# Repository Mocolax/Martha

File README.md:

# Martha: simulación, hardware y navegación PPO

Martha usa el mismo contrato ROS 2 en Gazebo y en el robot físico. El backend
se selecciona en el launch; teleoperación, RViz, SLAM y la política PPO no
cambian de tópicos.

| Interfaz | Simulación | Hardware |
|---|---|---|
| Comando | `/cmd_vel` (`Twist`) | `/cmd_vel` (`Twist`) |
| LiDAR | `/scan` | `/scan` |
| IMU | `/imu/data` | `/imu/data` |
| Odometría para consumidores | `/odometry/filtered` | `/odometry/filtered` |
| Meta | `/goal_pose` | `/goal_pose` |
| TF dinámico | `odom -> base_link` por EKF | `odom -> base_link` por EKF |
| Reloj | simulado | sistema |

SLAM Toolbox es la única autoridad de `map -> odom` cuando `mapping:=true`.
El controlador y el firmware entregan las mediciones de ruedas; el EKF es la
única autoridad dinámica de `odom -> base_link`.

## Construcción

Requiere Ubuntu 22.04 y ROS 2 Humble con Gazebo Classic. Desde el workspace:

```bash
cd ~/ros2_ws
rosdep install --from-paths src --ignore-src -r -y
python3 -m pip install -r src/martha/requirements-ppo.txt
colcon build --packages-select martha --symlink-install
source install/setup.bash
```

## Simulación

Arranque común sin SLAM:

```bash
ros2 launch martha bringup.launch.py mode:=sim mapping:=false
```

Este es el launcher canónico. `simulation.launch.py` y `hardware.launch.py`
son los backends que compone internamente.

Teleoperación, en otra terminal con el workspace cargado:

```bash
ros2 run teleop_twist_keyboard teleop_twist_keyboard \
  --ros-args -r cmd_vel:=/cmd_vel
```

Mapeo y RViz:

```bash
ros2 launch martha bringup.launch.py mode:=sim mapping:=true
```

Para guardar el mapa construido:

```bash
ros2 service call /slam_toolbox/save_map slam_toolbox/srv/SaveMap \
  "{name: {data: '/ruta/absoluta/mapa_martha'}}"
```

## Hardware

Antes del launch deben cumplirse estas condiciones:

1. La ESP32 ejecuta el firmware de `arduino/` y aparece en un puerto estable,
   preferiblemente `/dev/serial/by-id/...`.
2. El RPLIDAR A2M8 está conectado y tiene disponible el enlace estable
   `/dev/rplidar`.
3. La polaridad de motores y encoders, el radio de rueda y la geometría
   mecanum se comprobaron físicamente con las ruedas levantadas.

En cada computadora anfitriona, instala una vez la regla udev incluida en
`rplidar_ros` y vuelve a conectar el LiDAR:

```bash
sudo cp ~/ros2_ws/src/rplidar_ros/scripts/rplidar.rules \
  /etc/udev/rules.d/99-rplidar.rules
sudo udevadm control --reload-rules
sudo udevadm trigger
ls -l /dev/rplidar
```

El launch de hardware inicia `rplidar_node` con el perfil A2M8: 115200
baudios, modo `Sensitivity`, compensación angular, 10 Hz, tópico `/scan` y
frame `lidar`. Arranque completo:

```bash
ros2 launch martha bringup.launch.py \
  mode:=hardware \
  port:=/dev/serial/by-id/PUERTO_DE_LA_ESP32 \
  lidar_port:=/dev/rplidar \
  mapping:=true
```

El puerto puede sobrescribirse con `lidar_port:=...`. Si la ESP32 también usa
un adaptador CP210x, utiliza rutas distintas de `/dev/serial/by-id`; el launch
rechaza ambos argumentos si terminan apuntando al mismo dispositivo. Para usar
un driver iniciado externamente, añade `start_lidar:=false`.

El URDF sitúa el plano del LiDAR al frente y centrado, aproximadamente a
`x=0.2325 m` de `base_link`. El montaje físico debe respetar esa posición; si
cambia, deben actualizarse juntos el URDF y el offset usado por la protección
de huella PPO.

El mismo comando de `teleop_twist_keyboard` usado en simulación mueve el
hardware. Comprobaciones mínimas:

```bash
ros2 topic hz /scan
ros2 topic echo --once /scan
ros2 topic hz /odometry/filtered
ros2 topic echo --once /hardware/motor_fault
ros2 run tf2_ros tf2_echo odom base_link
ros2 run tf2_ros tf2_echo base_link lidar
```

El puente limita los comandos a `vx=0.35 m/s`, `vy=0.35 m/s` y
`wz=0.80 rad/s`; rechaza valores no finitos, vigila la telemetría serial y
publica el fault latched `/hardware/motor_fault`. Para rearmar una protección:

```bash
ros2 service call \
  /cmd_vel_serial_bridge/reset_motor_protection \
  std_srvs/srv/Trigger "{}"
ros2 topic pub --once /cmd_vel geometry_msgs/msg/Twist "{}"
```

El segundo comando cero debe enviarse después del reconocimiento de la ESP32.

## Entrenamiento PPO en Gazebo

Los escenarios canónicos son `four_rooms`, `hall`, `multi`, `roblab`, `room`
y `tube`. El entrenamiento genera un único mundo temporal con las seis arenas
en una cuadrícula 3×2, separadas 30 m, y lanza ocho robots namespaced
(`martha_0` a `martha_7`) dentro de un solo `gzserver`.

Los inicios y metas se editan únicamente en `config/training_points.yaml`.
Cada coordenada es local al `.world`; el coordinador aplica el desplazamiento
de su arena. `x` e `y` son obligatorios y `yaw: null` pide una orientación de
inicio aleatoria. Un mismo punto puede ser inicio o meta, pero no ambos para la
misma Martha. Antes de lanzar Gazebo se validan IDs, valores finitos, espacio
libre, conectividad, distancia mínima y ocho inicios simultáneos separados. No
hay generación automática: mientras una sección tenga menos de ocho puntos
válidos, `ppo_train` termina indicando el mapa problemático.

La observación contiene cuatro frames distribuidos durante un segundo de tiempo
ROS. Cada frame reúne 36 sectores LiDAR, distancia normalizada y seno/coseno del
rumbo hacia un waypoint local, además de velocidad odométrica `[Vx, Vy, W]`; el
vector completo tiene 168 valores. La distancia se codifica sin recorte como
`d / (d + 3 m)`. En Gazebo, el planificador privilegiado usa el mapa y la pose
real para actualizar un waypoint geodésico a 0.50 m; la política solo recibe
sus tres características relativas, no el mapa ni las coordenadas globales.
La llegada y las métricas siguen midiéndose contra la meta final. En el robot
real, un planificador global con localización debe producir el mismo waypoint.
La recompensa combina avance, penalización por paso, esfuerzo, cambios bruscos,
proximidad, colisión y llegada.

Cada robot publica contactos de su huella elevada en
`/martha_N/contacts` mediante `libgazebo_ros_bumper.so`. Los contactos con
suelo o con el propio modelo se ignoran; una pared u otra Martha finaliza el
episodio. Si chocan dos robots, ambos terminan. El LiDAR no decide colisiones:
se conserva para observación, recompensa de proximidad y validación del reset.

La cantidad original de puntos de `/scan` no cambia el tamaño del modelo: los
scans de densidad variable del A2M8 se agrupan angularmente por mínimo en los
mismos 36 sectores y se limitan al alcance común de 8 m.

El actor y el crítico tienen extractores multirrama independientes. La variable
`OBSERVATION_ENCODER_MODE` de `martha/PPO/network.py` selecciona `"present"`
(solo el frame más reciente) o `"history"` (los cuatro frames) como entrada de
las ramas de LiDAR, distancia, orientación y velocidad. El modo normal es
`"present"`; el entorno conserva el vector canónico de 168 valores, pero el
extractor ignora los tres frames antiguos y deja la temporalidad al LSTM. Las
ramas se fusionan en 384 unidades y luego el actor y el crítico usan su propia
LSTM de 128 unidades. Cambiar el modo exige entrenar un checkpoint nuevo.
Cada robot conserva memoria recurrente independiente; se borra al iniciar un
episodio, cambiar de meta, llegar o entrar en fault. PPO entrena fragmentos
ordenados de 32 pasos con máscaras de padding y de fin de episodio, sin barajar
transiciones temporales aisladas. Sus gradientes se recortan por separado. La
recompensa guardada en el
buffer se multiplica por `reward_scale` (`0.01` por defecto), pero
`episode_reward` conserva la recompensa original y `episode_scaled_reward`
registra el valor usado por PPO.

Los valores de entrenamiento estan reunidos al principio de
`martha/PPO/train.py`, en `TrainingDefaults`. Para cambiar permanentemente el
numero de robots, velocidad, episodios o hiperparametros, edita ese unico
bloque. El unico argumento de consola es `--resume`.

Las ocho Marthas comparten un escenario durante una ronda. Sus inicios no se
repiten; cada meta difiere del inicio propio. Al terminar por meta, contacto o
timeout, el robot se detiene, pierde su marcador y se teletransporta a una
plaza exclusiva alrededor de `y=-43 m`. Allí espera sin bloquear la arena.
Cuando termina la última Martha activa comienza la ronda siguiente. Cada ciclo
baraja los seis escenarios con la semilla del entrenamiento y usa cada uno una
sola vez. `map_index` fija todas las rondas a un único escenario. `episodes`
sigue contando episodios individuales, por lo que la última ronda puede activar
menos de ocho robots.

La recompensa se configura en `martha/PPO/reward.py`, dentro de
`RewardConfig`. Sigue la función completa de Jestel et al.,
[*Obtaining Robust Control and Navigation Policies for Multi-Robot Navigation
via Deep Reinforcement Learning*](https://arxiv.org/pdf/2209.03097). Para un
step no terminal se calcula:

```text
delta_d = distancia_euclidea_anterior - distancia_euclidea_actual
distancia = delta_d * (0.002 si delta_d < 0, de otro modo 0.01)
orientacion = (1 - 2 * abs(angulo_meta) / pi) *
              0.001, solo si Martha apunta a ±90° de la meta; si no, 0
record = 0.05 * (mejor_distancia_del_episodio - distancia_actual)
         solo cuando establece un nuevo récord
laser = -0.01 * (0.65 - minimo_laser), solo bajo 0.65 m
zigzag = -0.01, si hay más de 3 reversos directos izquierda-derecha
          durante las últimas 10 acciones
reward = costo_temporal + distancia + orientacion + record + laser + zigzag
```

La distancia para recompensa es euclídea; la distancia geodésica de Gazebo se
mantiene únicamente para SPL y las métricas de ruta. Cada transición no terminal
aplica un costo temporal de `-0.0002`. Los finales son exclusivos: meta `+1.0`,
colisión/motor fault/fuera del mapa `-0.75` y timeout `-0.5`.
Una colisión conserva prioridad sobre una señal simultánea de meta. El zigzag
usa la velocidad angular aplicada: izquierda por encima de `+0.2 rad/s`,
derecha por debajo de `-0.2 rad/s`; una acción recta corta la secuencia. Esos
tres parámetros no fueron publicados por el paper y son la adaptación acordada
para Martha. Los checkpoints nuevos guardan `reward_config`; al reanudar o
evaluar uno antiguo se usan los valores actuales y aparece una advertencia.

El entrenamiento siempre administra su propia instancia de Gazebo. No
inicies `simulation.launch.py` antes de `ppo_train`, ni siquiera cuando
`num_envs=1`. El perfil PPO usa por defecto un paso físico de 2 ms, 180 rayos
LiDAR reducidos a los mismos 36 sectores y cinemática planar. La simulación
normal conserva por defecto el modelo detallado de 48 rodillos por robot, el
paso de 1 ms y 360 rayos. Por tanto, el contrato de observación y los tópicos
ROS son comunes, pero el backend de entrenamiento evita simular articulaciones
que no aportan información a la política.

Si el factor supera la capacidad del equipo, Gazebo simplemente no alcanzara
la velocidad solicitada y pueden aparecer jitter, colas de mensajes o
`sensor_timeout` en las metricas. En ese caso reduce el factor; aumentar el
valor mas alla del rendimiento sostenible no acelera el aprendizaje.

Para entrenar:

```bash
cd ~/ros2_ws
source install/setup.bash
ros2 run martha ppo_train
```

`TrainingDefaults.num_envs=4` significa cantidad de robots, no cantidad de
servidores. En cada paso vectorizado el coordinador publica todas las acciones,
reanuda la física una vez, recibe sensores/contactos frescos y la pausa una
vez. Cuando uno termina, su plaza se recicla en el mismo mapa; el intervalo de
asentamiento se registra como transición de parada para los robots activos y
queda enmascarado del loss del actor, aunque sí entrena al crítico. El único log
de simulación queda en `<run>/gazebo.log`. Con `gazebo_gui=True`, una ventana
muestra las seis arenas y la flota.
El arranque es secuencial para evitar carreras de Gazebo y puede tardar varios
minutos con los modelos detallados; `gazebo_startup_timeout` vale 240 s.

Las evaluaciones periódicas esperan el final de un bloque. Los demás robots quedan
aparcados y `martha_0` evalúa la política dentro del mismo `gzserver`. Cambia
`eval_every`, `eval_map_count`, `num_envs`, `map_batch_episodes` y
`sim_speed_factor` en
`TrainingDefaults`; `eval_every=0` desactiva la evaluación periódica. En
entrenamiento no abras otro `simulation.launch.py`: el coordinador es dueño de
la única simulación.

Cada intento deja de asignar episodios 30 minutos antes del límite de 24 horas,
drena los episodios activos y guarda un checkpoint. Si alcanza el límite duro,
los episodios restantes se cierran como truncamientos con bootstrap. El CSV
incluye tiempo acumulado de física, reset, PPO, evaluación y checkpoint, además
de `training_steps_per_second`.

Cuando no haya un entrenamiento activo, compara 1, 2 y 4 robots con una carga
fija y sin actualizar la política:

```bash
ros2 run martha ppo_benchmark
```

El benchmark se niega a competir por recursos si detecta `ppo_train` activo.
Para validar ademas el reciclaje de un robot mientras sus pares siguen activos:

```bash
ros2 run martha ppo_benchmark --robot-counts 4 --steps 40 --recycle-smoke
```

Los resultados quedan por defecto en
`~/ros2_ws/src/martha/martha/PPO/ppo_runs/<run>/`: `metrics.csv`,
`last_model.pt`, `best_model.pt`, `learning_report.png`,
`ppo_diagnostics.png` y `training_summary.txt`. Los tres informes se generan
automáticamente al finalizar correctamente. El mejor modelo se elige por tasa de éxito,
SPL, menor tasa de colisión y, al final, recompensa. La ubicación se configura
con `TrainingDefaults.runs_dir`. `metrics.csv` incluye `approx_kl`,
`clip_fraction`, `explained_variance`, `policy_std`, `actor_inactive_relu` y
`critic_inactive_relu` para detectar inestabilidad antes de que la politica
deje de responder a sus observaciones. Para continuar un checkpoint se debe
conservar el mismo `reward_scale`:

```bash
ros2 run martha ppo_train \
  --resume /ruta/ppo_runs/run/last_model.pt
```

Antes de reanudar, establece en `TrainingDefaults.episodes` el episodio final
deseado. El CSV del run debe usar el esquema actual. La arquitectura LSTM usa
el contrato de política versión 5; los checkpoints feed-forward anteriores se
rechazan explícitamente y requieren comenzar un run nuevo o una transferencia
de pesos diseñada por separado.

Si el entrenamiento fue interrumpido o quieres volver a graficar un run
anterior, el siguiente comando usa el run modificado más recientemente:

```bash
ros2 run martha ppo_plot
```

También acepta directamente una carpeta de run o su `metrics.csv`:

```bash
ros2 run martha ppo_plot /ruta/ppo_runs/ppo_martha_YYYYMMDD_HHMMSS
```

La ventana de la media móvil se cambia en `REPORT_WINDOW`, al principio de
`martha/PPO/analytics.py`. Los runs nuevos guardan además la contribución
acumulada de cada término de `RewardConfig`, para identificar si dominan el
progreso, el costo temporal, el zigzag, el clearance o las recompensas terminales.

La exploración PPO también tiene tres fases configurables en `TrainingDefaults`:
`entropy_coef` se mantiene durante `entropy_exploration_fraction` (60 % por
defecto) de los episodios, disminuye linealmente hasta cero durante
`entropy_decay_fraction` (30 %), y queda en cero durante el porcentaje
restante. No modifica la recompensa, arquitectura ni learning rate; solo deja
de incentivar entropía para que PPO pueda consolidar una menor desviación
estándar cuando sus ventajas lo indiquen. El estado de la fase depende del
progreso relativo de los episodios, por lo que la misma configuración conserva
la fase al reanudar un checkpoint.

Evaluación determinista en los seis escenarios (requiere la simulación normal
ya iniciada en otra terminal):

```bash
ros2 launch martha simulation.launch.py gui:=false \
  sim_speed_factor:=5.0 physics_step_size:=0.002 \
  training_kinematic:=true lidar_samples:=180 lidar_visualize:=false

# En otra terminal, con el mismo workspace cargado:
ros2 run martha ppo_evaluate \
  --checkpoint /ruta/ppo_runs/run/best_model.pt
```

Configura backend, mapas, repeticiones, meta y CSV en `EvaluationDefaults`, al
principio de `martha/PPO/evaluate.py`.

## Ejecutar una política entrenada

El mismo launch sirve para ambos backends. Este checkpoint es un controlador
local: `/goal_pose` debe contener un waypoint aproximadamente 0.50 m por delante
sobre una ruta global, no la meta final seleccionada directamente con
**2D Goal Pose**. El planificador debe actualizarlo antes de que quede a 0.25 m;
las actualizaciones durante una navegación conservan la memoria LSTM.

```bash
# Gazebo
ros2 launch martha ppo_navigation.launch.py \
  mode:=sim checkpoint:=/ruta/best_model.pt mapping:=true

# Robot físico; el driver de /scan debe estar activo antes
ros2 launch martha ppo_navigation.launch.py \
  mode:=hardware \
  port:=/dev/serial/by-id/PUERTO_DE_LA_ESP32 \
  checkpoint:=/ruta/best_model.pt \
  mapping:=true
```

Sensores obsoletos, salida inválida, obstáculo dentro de la huella o un fault
del motor detienen y enclavan la política. Una meta nueva no borra el fault.
Después de resolver su causa:

```bash
ros2 service call /ppo_policy/rearm std_srvs/srv/Trigger "{}"
```

Luego se debe publicar una meta nueva.

No ejecutes `teleop_twist_keyboard` y `ppo_policy` al mismo tiempo: ambos son
productores directos de `/cmd_vel` y este proyecto todavía no incluye un mux
de prioridad. Usa teleoperación con `bringup.launch.py` o autonomía con
`ppo_navigation.launch.py`, de forma mutuamente exclusiva.

El entorno también permite entrenamiento y evaluación física. Configura
`backend="hardware"` y `goal=(X, Y)` en el bloque de valores correspondiente.
Cada episodio exige una confirmación interactiva, un operador presente y una
parada de emergencia. Para aprender normalmente se recomienda Gazebo y usar en
hardware el nodo de inferencia.

## Validación

Pruebas puras y contractuales:

```bash
python3 -m pytest -q
```

La prueba live administra su propio Gazebo y comprueba un `gzserver`, las seis
arenas, ocho Marthas y sus ocho tópicos de contacto independientes:

```bash
MARTHA_GAZEBO_SMOKE=1 python3 -m pytest -q -s \
  test/test_gazebo_env_smoke.py
```

Que el proyecto compile o pase en Gazebo no valida por sí solo la polaridad,
escala de encoders, deriva de IMU ni posición real del LiDAR. Esas cuatro
comprobaciones se deben cerrar sobre el robot físico antes de navegación
autónoma.

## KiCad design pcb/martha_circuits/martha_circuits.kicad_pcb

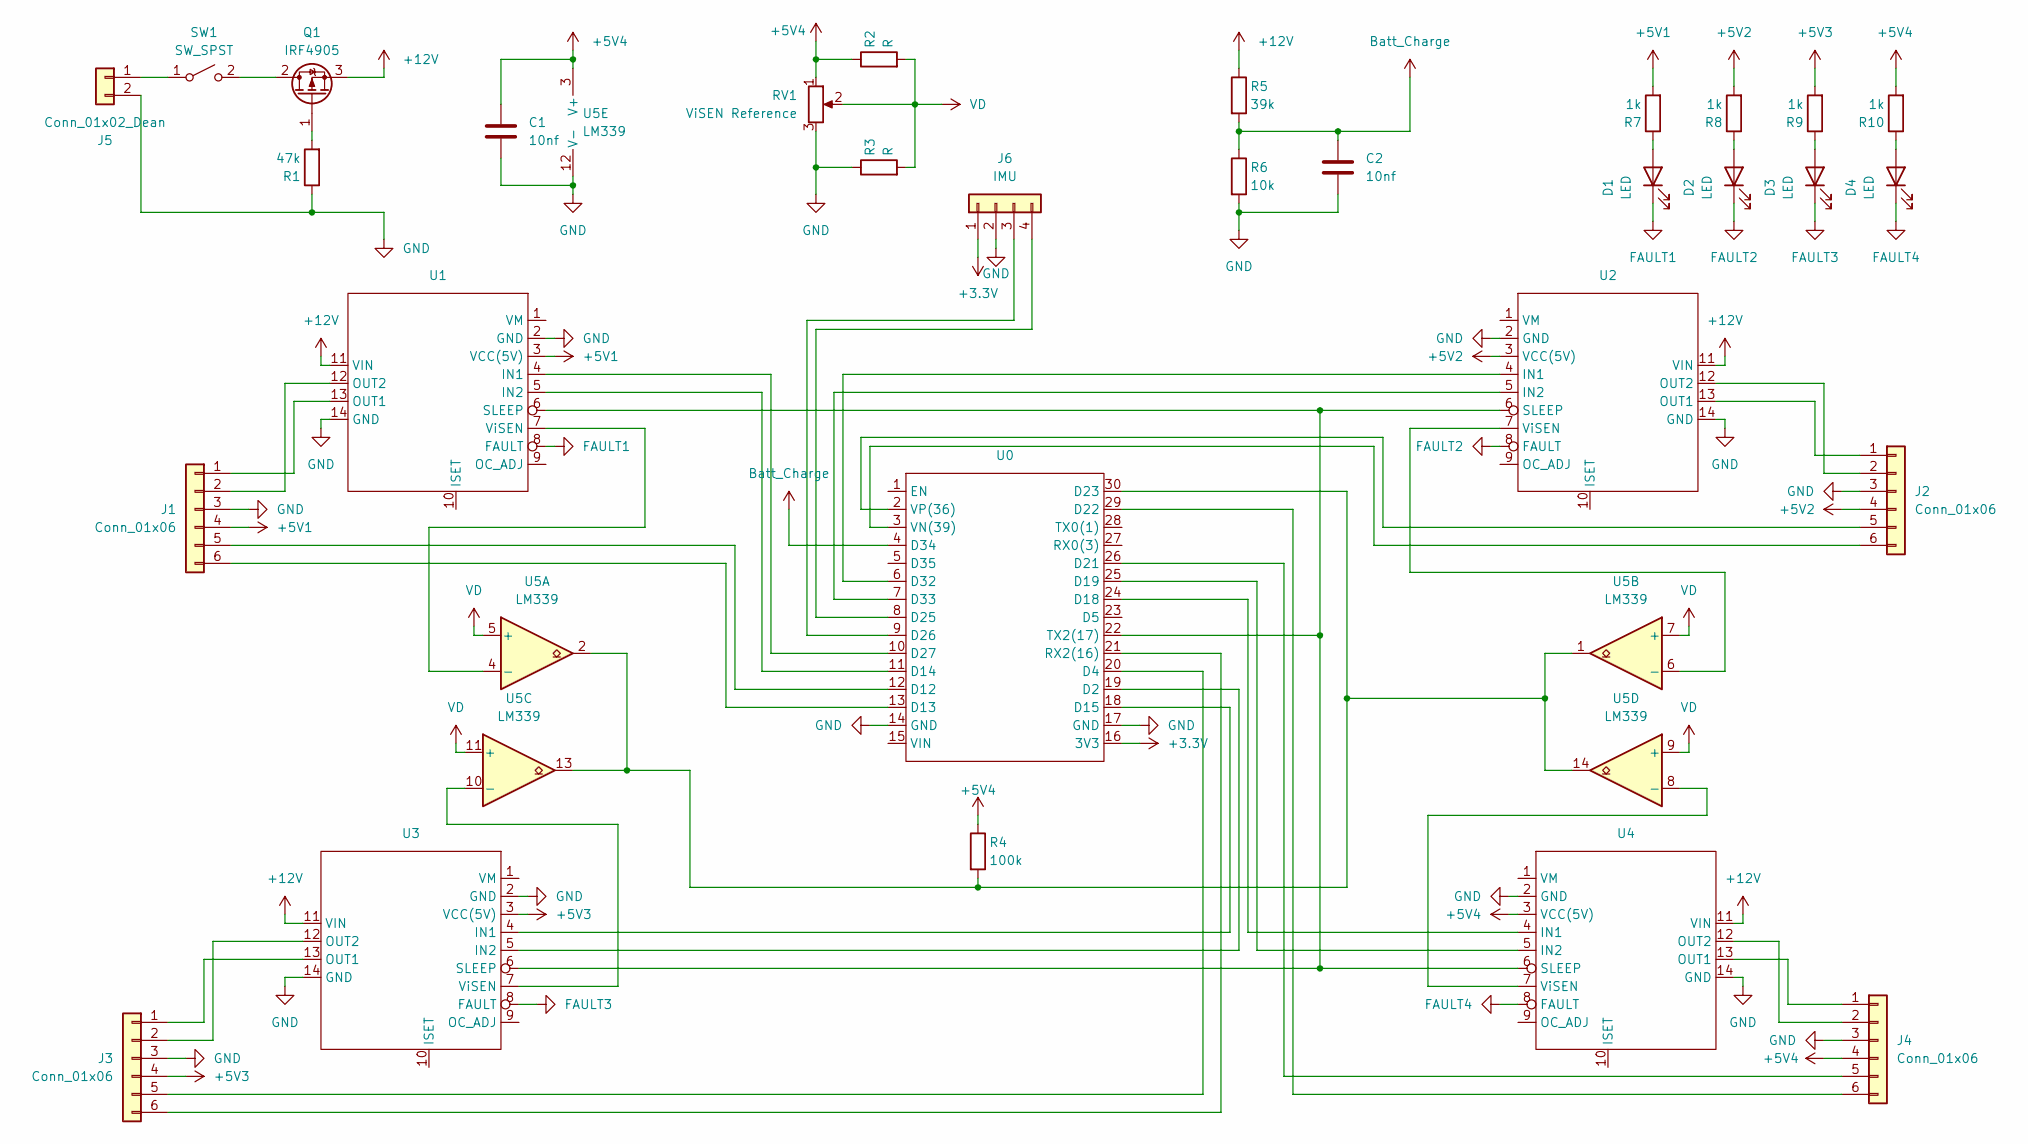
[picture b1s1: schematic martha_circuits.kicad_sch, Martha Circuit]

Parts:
C1, C2: 10nf; C_Disc_D5.0mm_W2.5mm_P2.50mm
D1, D2, D3, D4: LED; LED_D5.0mm
J1, J2, J3, J4: Conn_01x06; PinHeader_1x06_P2.54mm_Horizontal_Mirrored
J5: Conn_01x02_Dean; DEANS
J6: IMU; PinHeader_1x08_P2.54mm_Vertical
Q1: IRF4905; TO-220-3_Vertical
R1: 47k; R_Axial_DIN0207_L6.3mm_D2.5mm_P7.62mm_Horizontal
R2, R3: R; R_Axial_DIN0207_L6.3mm_D2.5mm_P7.62mm_Horizontal
R4: 100k; R_Axial_DIN0207_L6.3mm_D2.5mm_P7.62mm_Horizontal
R5: 39k; R_Axial_DIN0207_L6.3mm_D2.5mm_P7.62mm_Horizontal
R6: 10k; R_Axial_DIN0207_L6.3mm_D2.5mm_P7.62mm_Horizontal
R7, R8, R9, R10: 1k; R_Axial_DIN0207_L6.3mm_D2.5mm_P7.62mm_Horizontal
RV1: ViSEN Reference; Potentiometer_Bourns_3296W_Vertical
SW1: SW_SPST; SolderWire-0.75sqmm_1x02_P4.8mm_D1.25mm_OD2.3mm
U0: ESP32_DevKit_30Pin
U1, U2, U3, U4: MPQ6612A
U5: LM339; DIP-14_W7.62mm

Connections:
+3.3V: J6.1, U0.16 (3V3)
+5V1: J1.4, R7.2, U1.3 (VCC(5V))
+5V2: J2.4, R8.2, U2.3 (VCC(5V))
+5V3: J3.4, R9.2, U3.3 (VCC(5V))
+5V4: C1.1, J4.4, R2.1, R4.1, R10.2, RV1.1, U4.3 (VCC(5V)), U5.3 (V+)
+12V: Q1.3 (S), R5.1, U1.11 (VIN), U2.11 (VIN), U3.11 (VIN), U4.11 (VIN)
Batt_Charge: C2.1, R5.2, R6.1, U0.4 (D34)
FAULT1: D1.1 (K), U1.8 (FAULT)
FAULT2: D2.1 (K), U2.8 (FAULT)
FAULT3: D3.1 (K), U3.8 (FAULT)
FAULT4: D4.1 (K), U4.8 (FAULT)
GND: C1.2, C2.2, J1.3, J2.3, J3.3, J4.3, J5.2, J6.2, R1.1, R3.1, R6.2, RV1.3, U0.14 (GND), U0.17 (GND), U1.2 (GND), U1.14 (GND), U2.2 (GND), U2.14 (GND), U3.2 (GND), U3.14 (GND), U4.2 (GND), U4.14 (GND), U5.12 (V-)
unnamed: D1.2 (A), R7.1
unnamed: D2.2 (A), R8.1
unnamed: D3.2 (A), R9.1
unnamed: D4.2 (A), R10.1
unnamed: J1.1, U1.13 (OUT1)
unnamed: J1.2, U1.12 (OUT2)
unnamed: J1.5, U0.12 (D12)
unnamed: J1.6, U0.13 (D13)
unnamed: J2.1, U2.13 (OUT1)
unnamed: J2.2, U2.12 (OUT2)
unnamed: J2.5, U0.2 (VP(36))
unnamed: J2.6, U0.3 (VN(39))
unnamed: J3.1, U3.13 (OUT1)
unnamed: J3.2, U3.12 (OUT2)
unnamed: J3.5, U0.20 (D4)
unnamed: J3.6, U0.21 (RX2(16))
unnamed: J4.1, U4.13 (OUT1)
unnamed: J4.2, U4.12 (OUT2)
unnamed: J4.5, U0.26 (D21)
unnamed: J4.6, U0.29 (D22)
unnamed: J5.1, SW1.1 (A)
unnamed: J6.3, U0.9 (D26)
unnamed: J6.4, U0.8 (D25)
unnamed: Q1.2 (D), SW1.2 (B)
unnamed: Q1.1 (G), R1.2
unnamed: U0.19 (D2), U3.5 (IN2)
unnamed: U0.11 (D14), U1.5 (IN2)
unnamed: U0.18 (D15), U3.4 (IN1)
unnamed: U0.24 (D18), U4.4 (IN1)
unnamed: U0.25 (D19), U4.5 (IN2)
unnamed: R4.2, U0.30 (D23), U5.1, U5.2, U5.13, U5.14
unnamed: U0.10 (D27), U1.4 (IN1)
unnamed: U0.6 (D32), U2.4 (IN1)
unnamed: U0.7 (D33), U2.5 (IN2)
unnamed: U0.22 (TX2(17)), U1.6 (SLEEP), U2.6 (SLEEP), U3.6 (SLEEP), U4.6 (SLEEP)
unnamed: U1.7 (ViSEN), U5.4 (-)
unnamed: U2.7 (ViSEN), U5.6 (-)
unnamed: U3.7 (ViSEN), U5.10 (-)
unnamed: U4.7 (ViSEN), U5.8 (-)
VD: R2.2, R3.2, RV1.2, U5.5 (+), U5.7 (+), U5.9 (+), U5.11 (+)

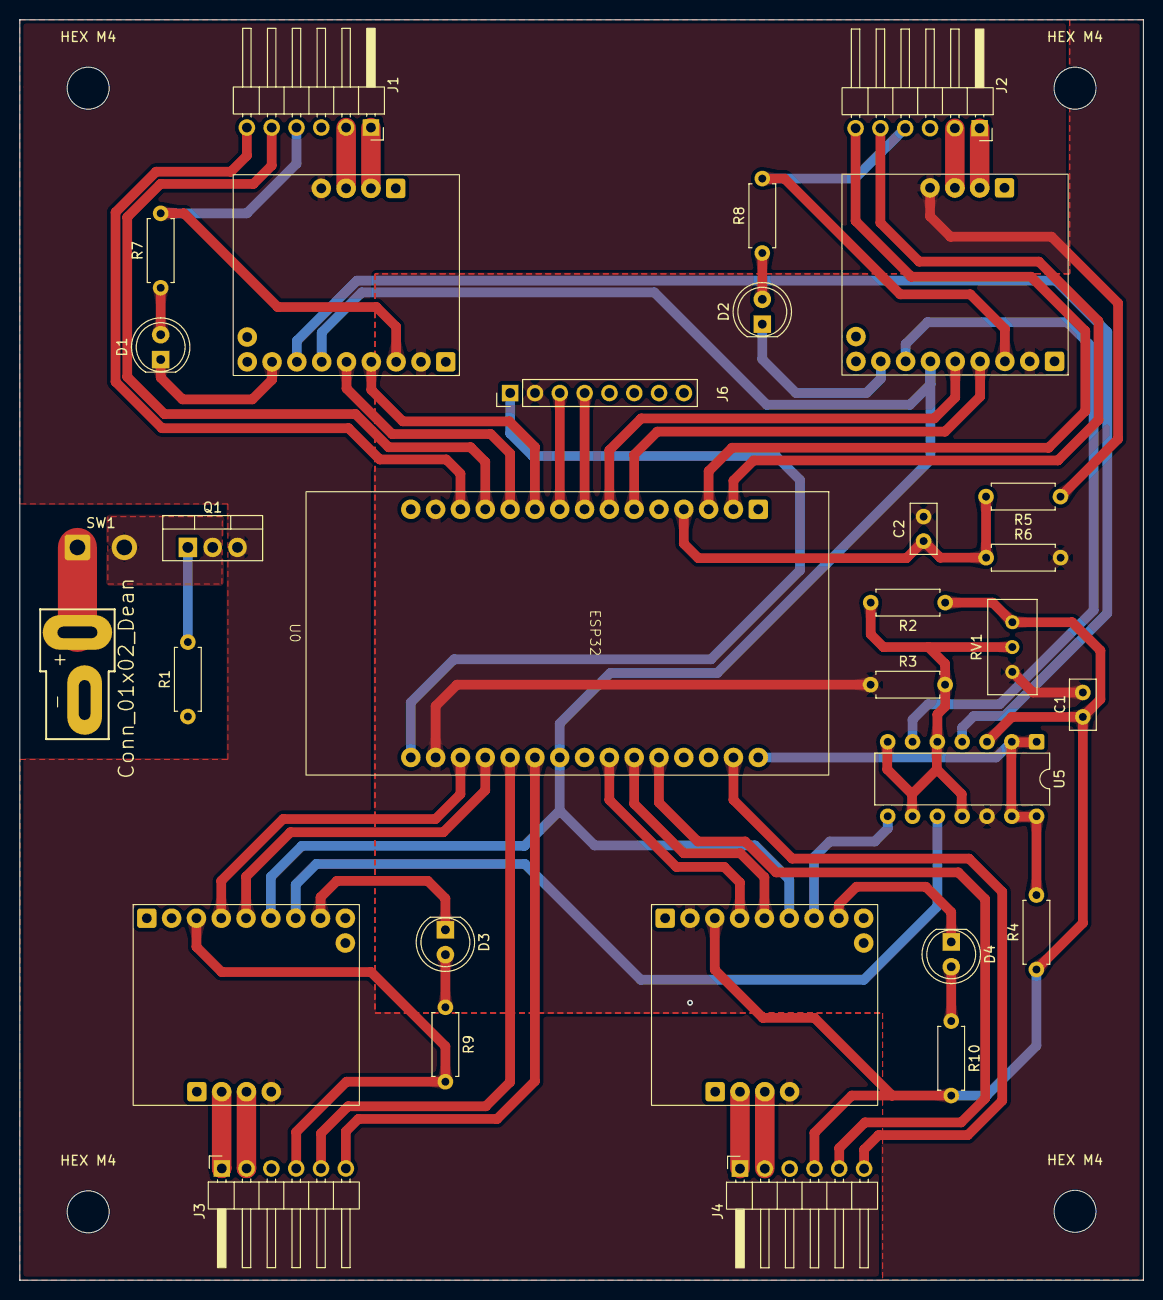
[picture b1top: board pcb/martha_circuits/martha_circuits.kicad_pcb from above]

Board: 2 copper layers, 115.0 x 129.0 mm, 35 parts (0 on the bottom side), 52 nets.

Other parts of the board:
HEX M4, HEX M4#2, HEX M4#3, HEX M4#4: MountingHole_4.3mm_M4

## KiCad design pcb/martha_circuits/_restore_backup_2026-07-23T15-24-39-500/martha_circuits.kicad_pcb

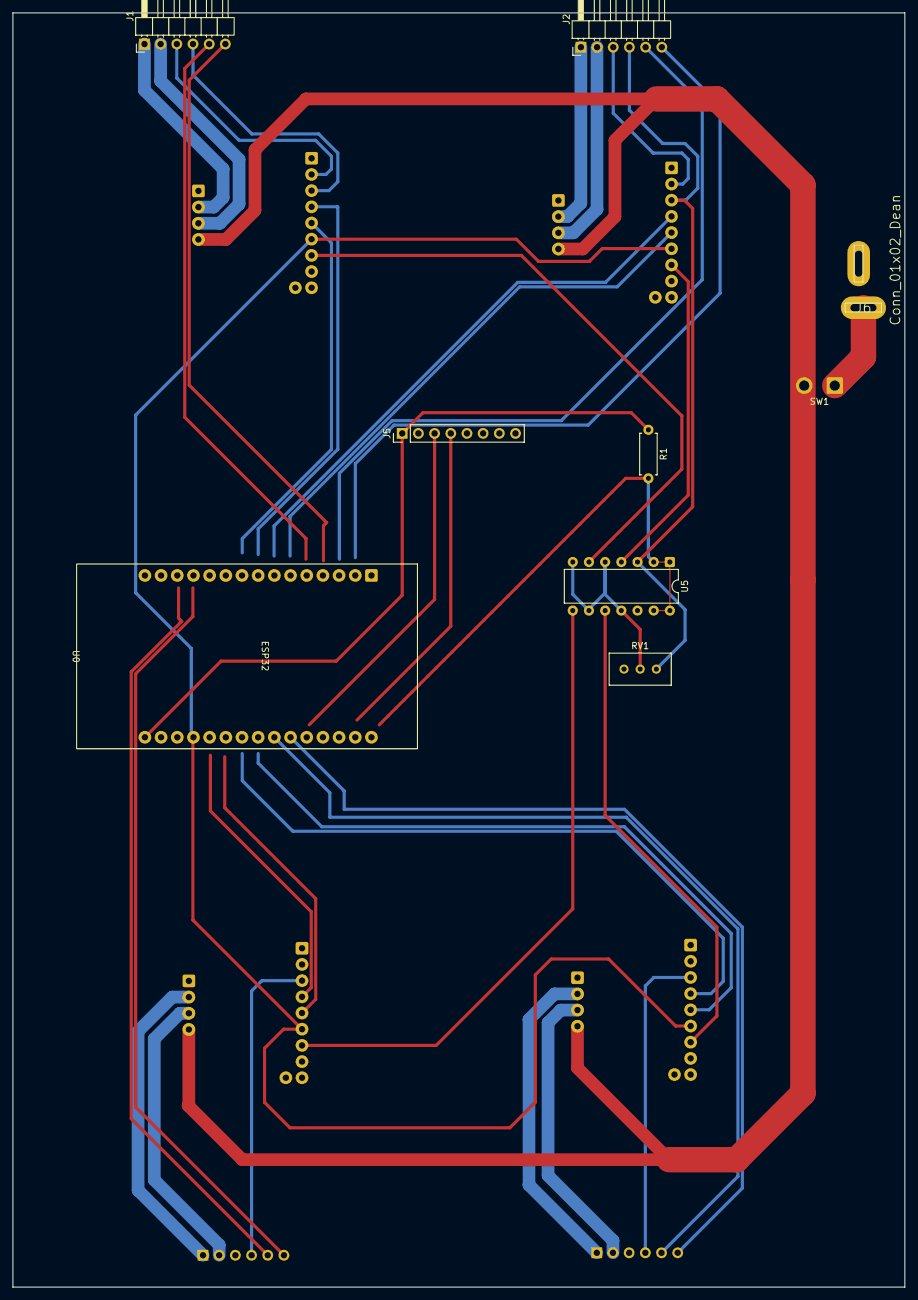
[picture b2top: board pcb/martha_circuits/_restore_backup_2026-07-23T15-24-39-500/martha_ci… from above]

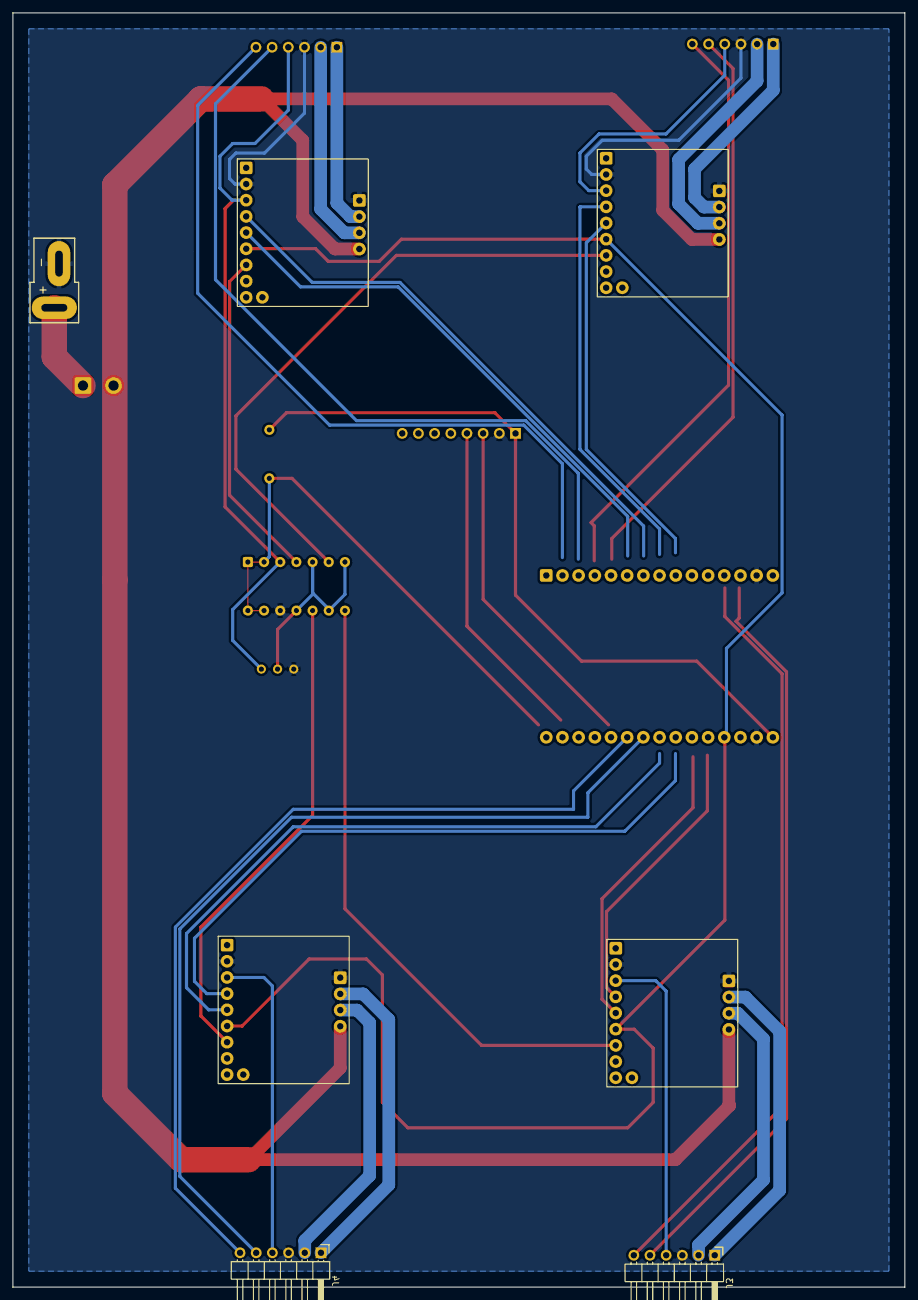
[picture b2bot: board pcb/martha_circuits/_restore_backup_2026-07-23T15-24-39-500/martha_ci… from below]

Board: 2 copper layers, 140.0 x 200.0 mm, 15 parts (6 on the bottom side), 41 nets.

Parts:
J1, J2, J3, J4: Conn_01x06; PinHeader_1x06_P2.54mm_Horizontal
J5: IMU; PinHeader_1x08_P2.54mm_Vertical
J6: Conn_01x02_Dean; DEANS
R1: R; R_Axial_DIN0207_L6.3mm_D2.5mm_P7.62mm_Horizontal
RV1: ViSEN Reference; Potentiometer_Bourns_3296W_Vertical
SW1: SW_SPST; SolderWire-0.75sqmm_1x02_P4.8mm_D1.25mm_OD2.3mm
U0: ESP32_DevKit_30Pin
U1, U2, U3, U4: MPQ6612A
U5: LM339; DIP-14_W7.62mm

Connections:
+3.3V: J5.1, R1.1, U0.16 (3V3)
+5V1: J1.4, U1.3 (VCC(5V))
+5V2: J2.4, RV1.1, U2.3 (VCC(5V)), U5.3 (V+)
+5V3: J3.4, U3.3 (VCC(5V))
+5V4: J4.4, U4.3 (VCC(5V))
+12V: SW1.2 (B), U1.11 (VIN), U2.11 (VIN), U3.11 (VIN), U4.11 (VIN)
GND: J1.3, J2.3, J3.3, J4.3, J5.2, J6.2, RV1.3, U0.14 (GND), U0.17 (GND), U1.2 (GND), U1.14 (GND), U2.2 (GND), U2.14 (GND), U3.2 (GND), U3.14 (GND), U4.2 (GND), U4.14 (GND), U5.12 (V-)
unnamed: J1.1, U1.13 (OUT1)
unnamed: J1.2, U1.12 (OUT2)
unnamed: J1.5, U0.4 (D34)
unnamed: J1.6, U0.5 (D35)
unnamed: J2.1, U2.13 (OUT1)
unnamed: J2.2, U2.12 (OUT2)
unnamed: J2.5, U0.2 (VP(36))
unnamed: J2.6, U0.3 (VN(39))
unnamed: J3.1, U3.13 (OUT1)
unnamed: J3.2, U3.12 (OUT2)
unnamed: J3.5, U0.6 (D32)
unnamed: J3.6, U0.7 (D33)
unnamed: J4.1, U4.13 (OUT1)
unnamed: J4.2, U4.12 (OUT2)
unnamed: J4.5, U0.24 (D18)
unnamed: J4.6, U0.25 (D19)
unnamed: J5.3, U0.29 (D22)
unnamed: J5.4, U0.26 (D21)
unnamed: J6.1, SW1.1 (A)
unnamed: U0.19 (D2), U1.6 (SLEEP), U2.6 (SLEEP), U3.6 (SLEEP), U4.6 (SLEEP)
unnamed: R1.2, U0.20 (D4), U5.1, U5.2, U5.13, U5.14
unnamed: U0.13 (D13), U4.5 (IN2)
unnamed: U0.11 (D14), U2.5 (IN2)
unnamed: U0.30 (D23), U4.4 (IN1)
unnamed: U0.8 (D25), U1.4 (IN1)
unnamed: U0.9 (D26), U1.5 (IN2)
unnamed: U0.10 (D27), U2.4 (IN1)
unnamed: U0.21 (RX2(16)), U3.4 (IN1)
unnamed: U0.22 (TX2(17)), U3.5 (IN2)
unnamed: U1.7 (ViSEN), U5.6 (-)
unnamed: U2.7 (ViSEN), U5.4 (-)
unnamed: U3.7 (ViSEN), U5.8 (-)
unnamed: U4.7 (ViSEN), U5.10 (-)
VD: RV1.2, U5.5 (+), U5.7 (+), U5.9 (+), U5.11 (+)

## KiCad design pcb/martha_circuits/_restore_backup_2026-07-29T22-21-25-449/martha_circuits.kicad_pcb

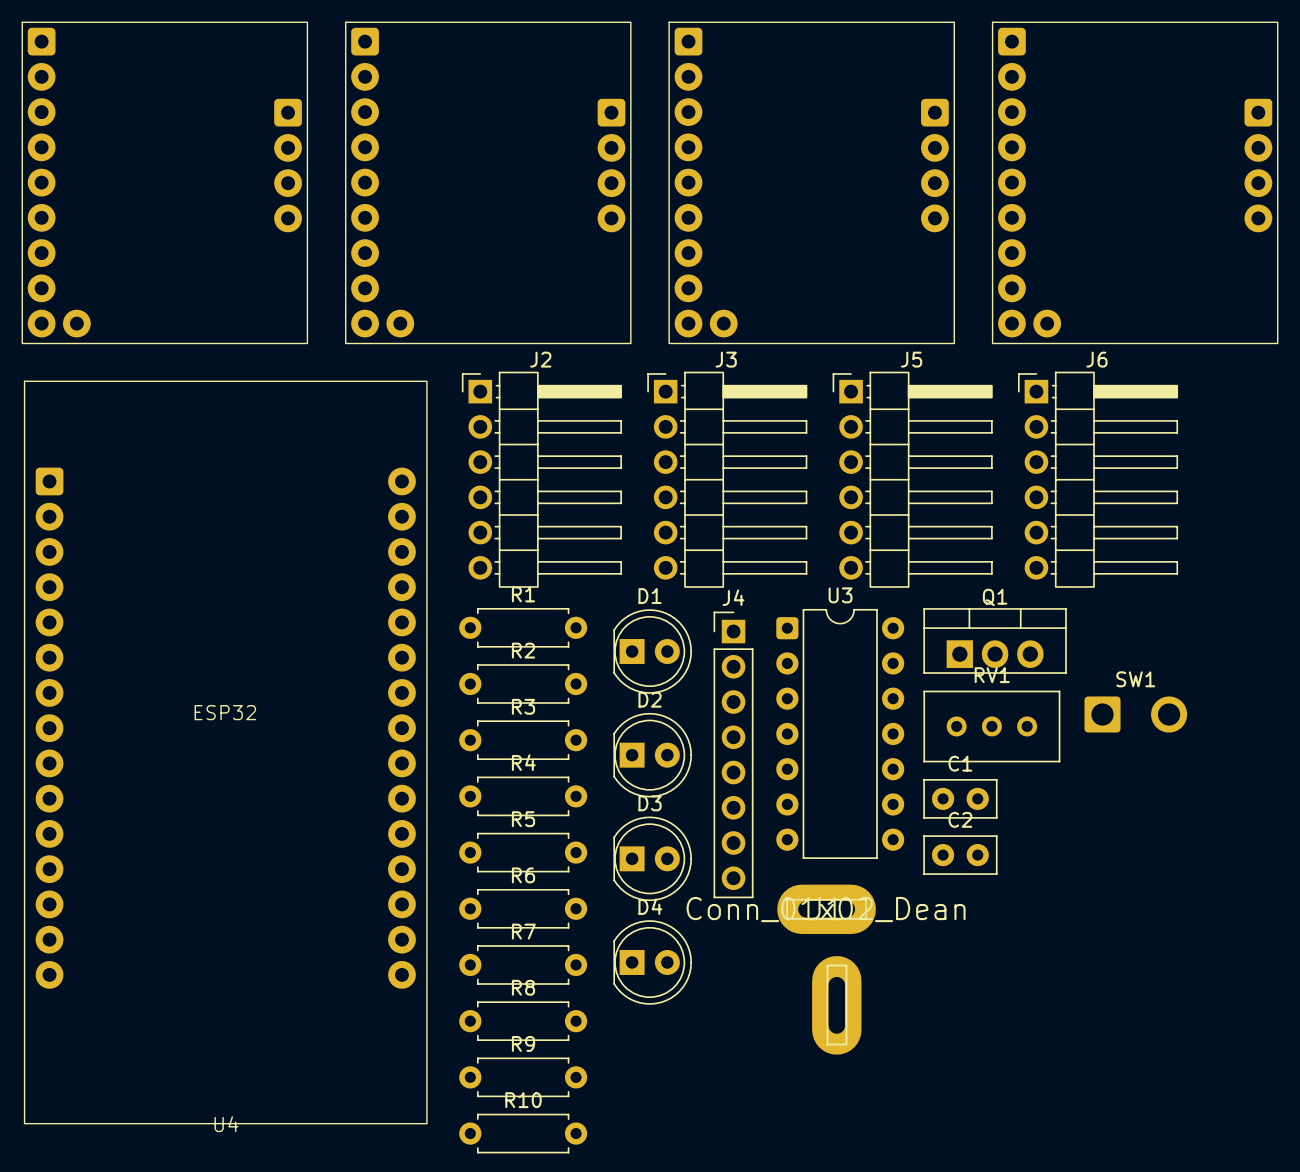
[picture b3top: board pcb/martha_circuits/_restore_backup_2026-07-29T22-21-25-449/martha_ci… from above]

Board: 2 copper layers, 31 parts (0 on the bottom side), 52 nets, no tracks yet.

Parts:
C1, C2: 10nf; C_Disc_D5.0mm_W2.5mm_P2.50mm
D1, D2, D3, D4: LED; LED_D5.0mm
J1: Conn_01x02_Dean; DEANS
J2, J3, J5, J6: Conn_01x06; PinHeader_1x06_P2.54mm_Horizontal
J4: IMU; PinHeader_1x08_P2.54mm_Vertical
Q1: IRF4905; TO-220-3_Vertical
R1: 47k; R_Axial_DIN0207_L6.3mm_D2.5mm_P7.62mm_Horizontal
R2, R3, R7, R8, R9, R10: R; R_Axial_DIN0207_L6.3mm_D2.5mm_P7.62mm_Horizontal
R4: 100k; R_Axial_DIN0207_L6.3mm_D2.5mm_P7.62mm_Horizontal
R5: 39k; R_Axial_DIN0207_L6.3mm_D2.5mm_P7.62mm_Horizontal
R6: 10k; R_Axial_DIN0207_L6.3mm_D2.5mm_P7.62mm_Horizontal
RV1: ViSEN Reference; Potentiometer_Bourns_3296W_Vertical
SW1: SW_SPST; SolderWire-0.75sqmm_1x02_P4.8mm_D1.25mm_OD2.3mm
U1, U2, U5, U6: MPQ6612A
U3: LM339; DIP-14_W7.62mm
U4: ESP32_DevKit_30Pin

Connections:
+3.3V: J4.1, R4.1, U4.16 (3V3)
+5V1: J3.4, R7.2, U2.3 (VCC(5V))
+5V2: C1.1, J6.4, R2.1, R8.2, RV1.1, U3.3 (V+), U5.3 (VCC(5V))
+5V3: J2.4, R9.2, R10.2, U1.3 (VCC(5V))
+5V4: J5.4, U6.3 (VCC(5V))
+12V: R5.1, SW1.2 (B), U1.11 (VIN), U2.11 (VIN), U5.11 (VIN), U6.11 (VIN)
FAULT1: D1.1 (K), U2.8 (FAULT)
FAULT2: D2.1 (K), U5.8 (FAULT)
FAULT3: D3.1 (K), U1.8 (FAULT)
FAULT4: D4.1 (K), U6.8 (FAULT)
GND: C1.2, C2.2, J1.2, J2.3, J3.3, J4.2, J5.3, J6.3, R1.1, R3.1, R6.2, RV1.3, U1.2 (GND), U1.14 (GND), U2.2 (GND), U2.14 (GND), U3.12 (V-), U4.14 (GND), U4.17 (GND), U5.2 (GND), U5.14 (GND), U6.2 (GND), U6.14 (GND)
unnamed: C2.1, R5.2, R6.1
unnamed: D1.2 (A), R7.1
unnamed: D2.2 (A), R8.1
unnamed: D3.2 (A), R9.1
unnamed: D4.2 (A), R10.1
unnamed: J1.1, Q1.2 (D)
unnamed: J2.1, U1.13 (OUT1)
unnamed: J2.2, U1.12 (OUT2)
unnamed: J2.5, U4.13 (D13)
unnamed: J2.6, U4.12 (D12)
unnamed: J3.1, U2.13 (OUT1)
unnamed: J3.2, U2.12 (OUT2)
unnamed: J3.5, U4.11 (D14)
unnamed: J3.6, U4.10 (D27)
unnamed: J4.3, U4.26 (D21)
unnamed: J4.4, U4.29 (D22)
unnamed: J5.1, U6.13 (OUT1)
unnamed: J5.2, U6.12 (OUT2)
unnamed: J5.5, U4.24 (D18)
unnamed: J5.6, U4.25 (D19)
unnamed: J6.1, U5.13 (OUT1)
unnamed: J6.2, U5.12 (OUT2)
unnamed: J6.5, U4.3 (VN(39))
unnamed: J6.6, U4.2 (VP(36))
unnamed: Q1.1 (G), R1.2
unnamed: Q1.3 (S), SW1.1 (A)
unnamed: U1.4 (IN1), U4.20 (D4)
unnamed: U1.5 (IN2), U4.21 (RX2(16))
unnamed: U1.6 (SLEEP), U2.6 (SLEEP), U4.19 (D2), U5.6 (SLEEP), U6.6 (SLEEP)
unnamed: U1.7 (ViSEN), U3.8 (-)
unnamed: U2.4 (IN1), U4.9 (D26)
unnamed: U2.5 (IN2), U4.8 (D25)
unnamed: U2.7 (ViSEN), U3.6 (-)
unnamed: U3.4 (-), U5.7 (ViSEN)
unnamed: U3.10 (-), U6.7 (ViSEN)
unnamed: U4.23 (D5), U6.5 (IN2)
unnamed: R4.2, U3.1, U3.2, U3.13, U3.14, U4.30 (D23)
unnamed: U4.6 (D32), U5.5 (IN2)
unnamed: U4.7 (D33), U5.4 (IN1)
unnamed: U4.22 (TX2(17)), U6.4 (IN1)
VD: R2.2, R3.2, RV1.2, U3.5 (+), U3.7 (+), U3.9 (+), U3.11 (+)

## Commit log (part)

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2025-09-05 Julian puto
2025-09-12 First Commit v2
2025-09-12 Commit test nuc
2025-09-30 Correccion setup y launch. Movimiento x,y y angular y lectura serial
2025-09-30 show speeds
2025-09-30 Recibir velocidad desde placa
2025-09-30 README.md
2025-10-07 Factorizacion ni la bestia, y primer intento odometria
2025-10-07 Parametros simulacion
2025-10-21 No se xd
